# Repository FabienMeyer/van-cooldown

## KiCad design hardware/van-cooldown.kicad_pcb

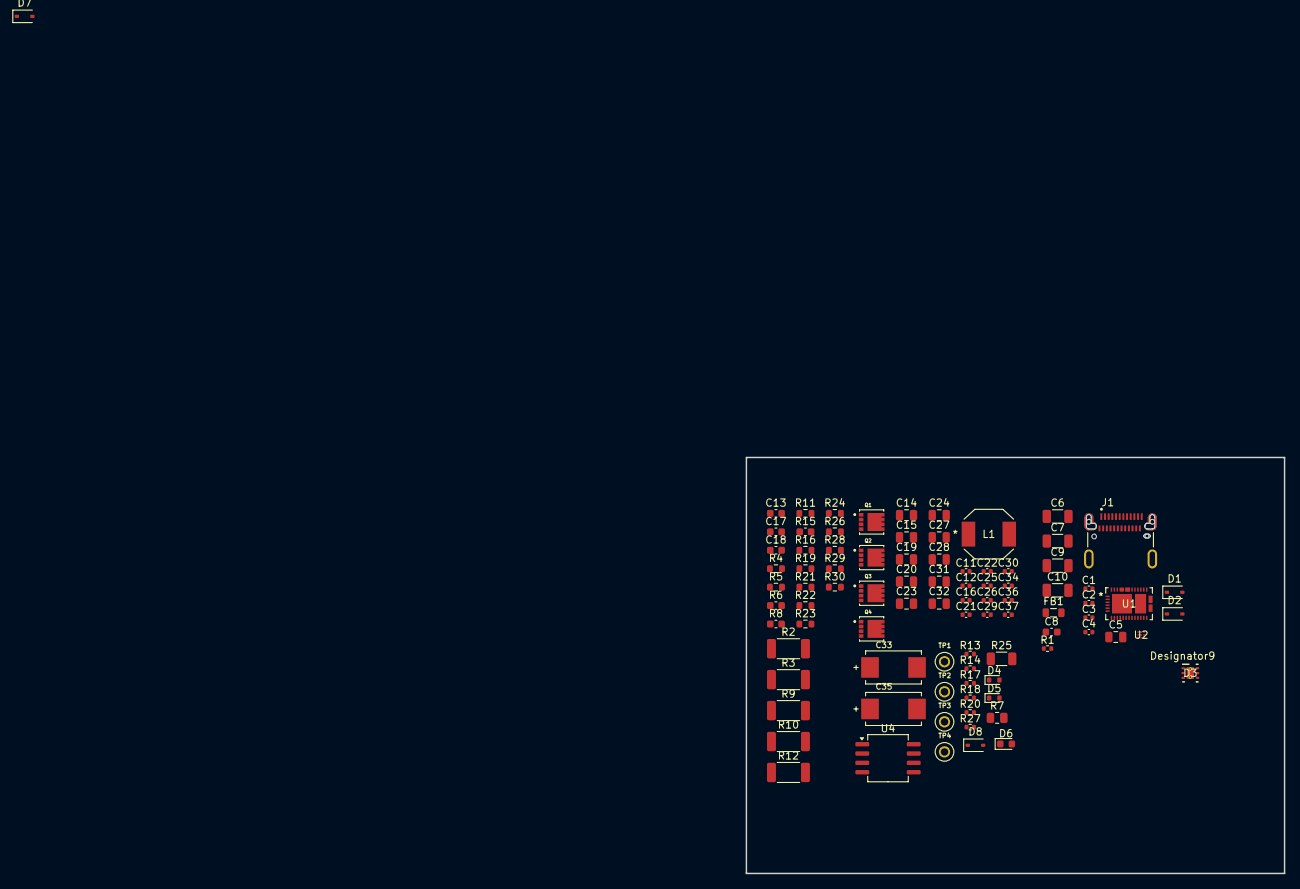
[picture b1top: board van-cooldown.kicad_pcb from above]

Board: 8 copper layers, 73.2 x 56.6 mm, 89 parts (0 on the bottom side), 12 nets, no tracks yet.

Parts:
C1, C2, C3, C4: 10000 pF; C_0402_1005Metric
C5: 4.7 uF; C_0805_2012Metric
C6, C7, C9, C10: 10 µF; C_1206_3216Metric
C8: 330 pF; C_0603_1608Metric
C11, C12: 1 nF; C_0402_1005Metric
C13, C17: 10 µF; C_0603_1608Metric
C14, C15, C19, C20, C23, C24, C27, C28, C31, C32: 10 µF; C_0805_2012Metric
C16, C21, C25, C26, C29, C30, C34: 0.1 µF; C_0402_1005Metric
C18: 4.7 uF; C_0603_1608Metric
C22: 1000 pF; C_0402_1005Metric
C33, C35: 33 µF; C_ECASD31D476M040KA0
C36, C37: 0.047 µF; C_0402_1005Metric
D1, D2: PESD5V0L1BA-115; D_SOD-323
D3: TVS2200DRVR; D_TVS2200DRVR
D4, D5: 12V; D_SOD-523
D6: Led Green; LED_0603_1608Metric
D7, D8: 30V 200mA; D_SOD-323
FB1: 21 Ω; L_0805_2012Metric
J1: DX07S024JJ2R1300; J_DX07S024JJ2R1300
L1: 1 µH; IND_SPM6530_TDK
Q1, Q2, Q3, Q4: CSD17575Q3; Q_CSD17575Q3
R1: 3.3 kOhms; R_0402_1005Metric
R2, R3, R9, R10, R12: 10 mOhms; R_2010_5025Metric
R4, R5: 294 Ω; R_0603_1608Metric
R6, R8: 0 Ω; C_0603_1608Metric
R7: 0 Ω; R_0805_2012Metric
R11: 100 kOhms; R_0603_1608Metric
R13: 5.23 kΩ; R_0402_1005Metric
R14: 30.1 kΩ; R_0402_1005Metric
R15: 100 Ω; C_0603_1608Metric
R16: 18 kΩ; R_0603_1608Metric
R17: 10 kΩ; R_0402_1005Metric
R18: 7.68 kΩ; R_0402_1005Metric
R19: 127 kΩ; R_0603_1608Metric
R20: 4.87 kΩ; R_0402_1005Metric
R21: 27 kΩ; R_0603_1608Metric
R22: 255 kΩ; R_0603_1608Metric
R23: 6.2 kOhms; R_0603_1608Metric
R24: 4.75 kΩ; R_0603_1608Metric
R25: 10 Ω; R_1206_3216Metric
R26: 3.57 kΩ; R_0603_1608Metric
R27: 2.21 kΩ; R_0402_1005Metric
R28: 8.2 kOhms; R_0603_1608Metric
R29: 14 kΩ; R_0603_1608Metric
R30: 10.5 kΩ; R_0603_1608Metric
TP1: TP Black; TP_5001
TP2: TP White; TP_5002
TP3: TP Orange; TP_5003
TP4: TP Red; TP_5000
U1: TPS25751SRSMR; IC_TPS25751DREFR
U2: TPD2S300YFFR; IC_TPD2S300YFFR
U4: CAT24C512WI-GT3; SOIC-8_5.3x6.2mm_P1.27mm

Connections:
/USB_N: D2.1, J1.A7 (DN1), J1.B7 (DN2)
/USB_P: D1.1, J1.A6 (DP1), J1.B6 (DP2)
/VBUS: C5.1, FB1.2
/charger/VBUS: Q3.5, Q3.6, Q3.7, Q3.8, Q3.9, Q4.1, Q4.2, Q4.3
unnamed: C11.1, D4.2 (A), Q1.1, Q1.2, Q1.3, Q3.1, Q3.2, Q3.3
unnamed: C11.2, D4.1 (K), Q1.4, Q3.4, R4.1
unnamed: C12.1, D5.2 (A), Q2.1, Q2.2, Q2.3, Q4.5, Q4.6, Q4.7, Q4.8, Q4.9
unnamed: C12.2, D5.1 (K), Q2.4, Q4.4, R5.1
unnamed: C1.1, C2.1, C3.1, C4.1, D3.4 (IN), D3.5 (IN), D3.6 (IN), FB1.1, J1.A4 (VBUSA1), J1.A9 (VBUSA2), J1.B4 (VBUSB1), J1.B9 (VBUSB2)
unnamed: Q1.5, Q1.6, Q1.7, Q1.8, Q1.9, R2.2
unnamed: Q2.5, Q2.6, Q2.7, Q2.8, Q2.9, R3.2
PGND: C1.2, C2.2, C3.2, C4.2, C5.2, D1.2, D2.2, D3.1 (GND), D3.2 (GND), D3.3 (GND), D3.7 (PAD), J1.A1 (GNDA1), J1.A12 (GNDA2), J1.B1 (GNDB1), J1.B12 (GNDB2), J1.S1 (SHIELD0), J1.S2 (SHIELD1), J1.S3 (SHIELD2), J1.S4 (SHIELD3)

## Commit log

2025-07-19 feat: add documentation and update board
2025-07-19 feat: add docker for documentation
2025-07-25 Add version information page to documentation
2025-07-25 Add comprehensive git information to documentation
    - Added mkdocs-git-committers-plugin for contributor information
    - Created git information macros in main.py for commit details
    - Enhanced footer with detailed git version information including:
    * Documentation version (commit count)
    * Commit hash and branch links
    * Last updated and build dates
2025-07-26 Add Vale prose linting to documentation workflow
    - Added Vale configuration (.vale.ini) with Microsoft, write-good, alex, and custom VanCooldown styles
    - Created custom VanCooldown vocabulary for technical terms
    - Added vale_check.py script for Vale integration
    - Updated docs_manager.py to include Vale in quality checks
    - Added VS Code tasks for Vale linting
    - Created comprehensive scripts README with Vale instructions
2025-08-01 clean reposirtoy
2025-08-01 feat: Add readme file
2025-08-01 feat: add gitignore file
2025-08-02 feat: basic mkdocs documentation
2025-08-02 feat: add mdformat
2025-08-02 fix: documentation configuration
2025-08-02 feat: mkdoc is configure
2025-08-03 feat: add some empty base pages
